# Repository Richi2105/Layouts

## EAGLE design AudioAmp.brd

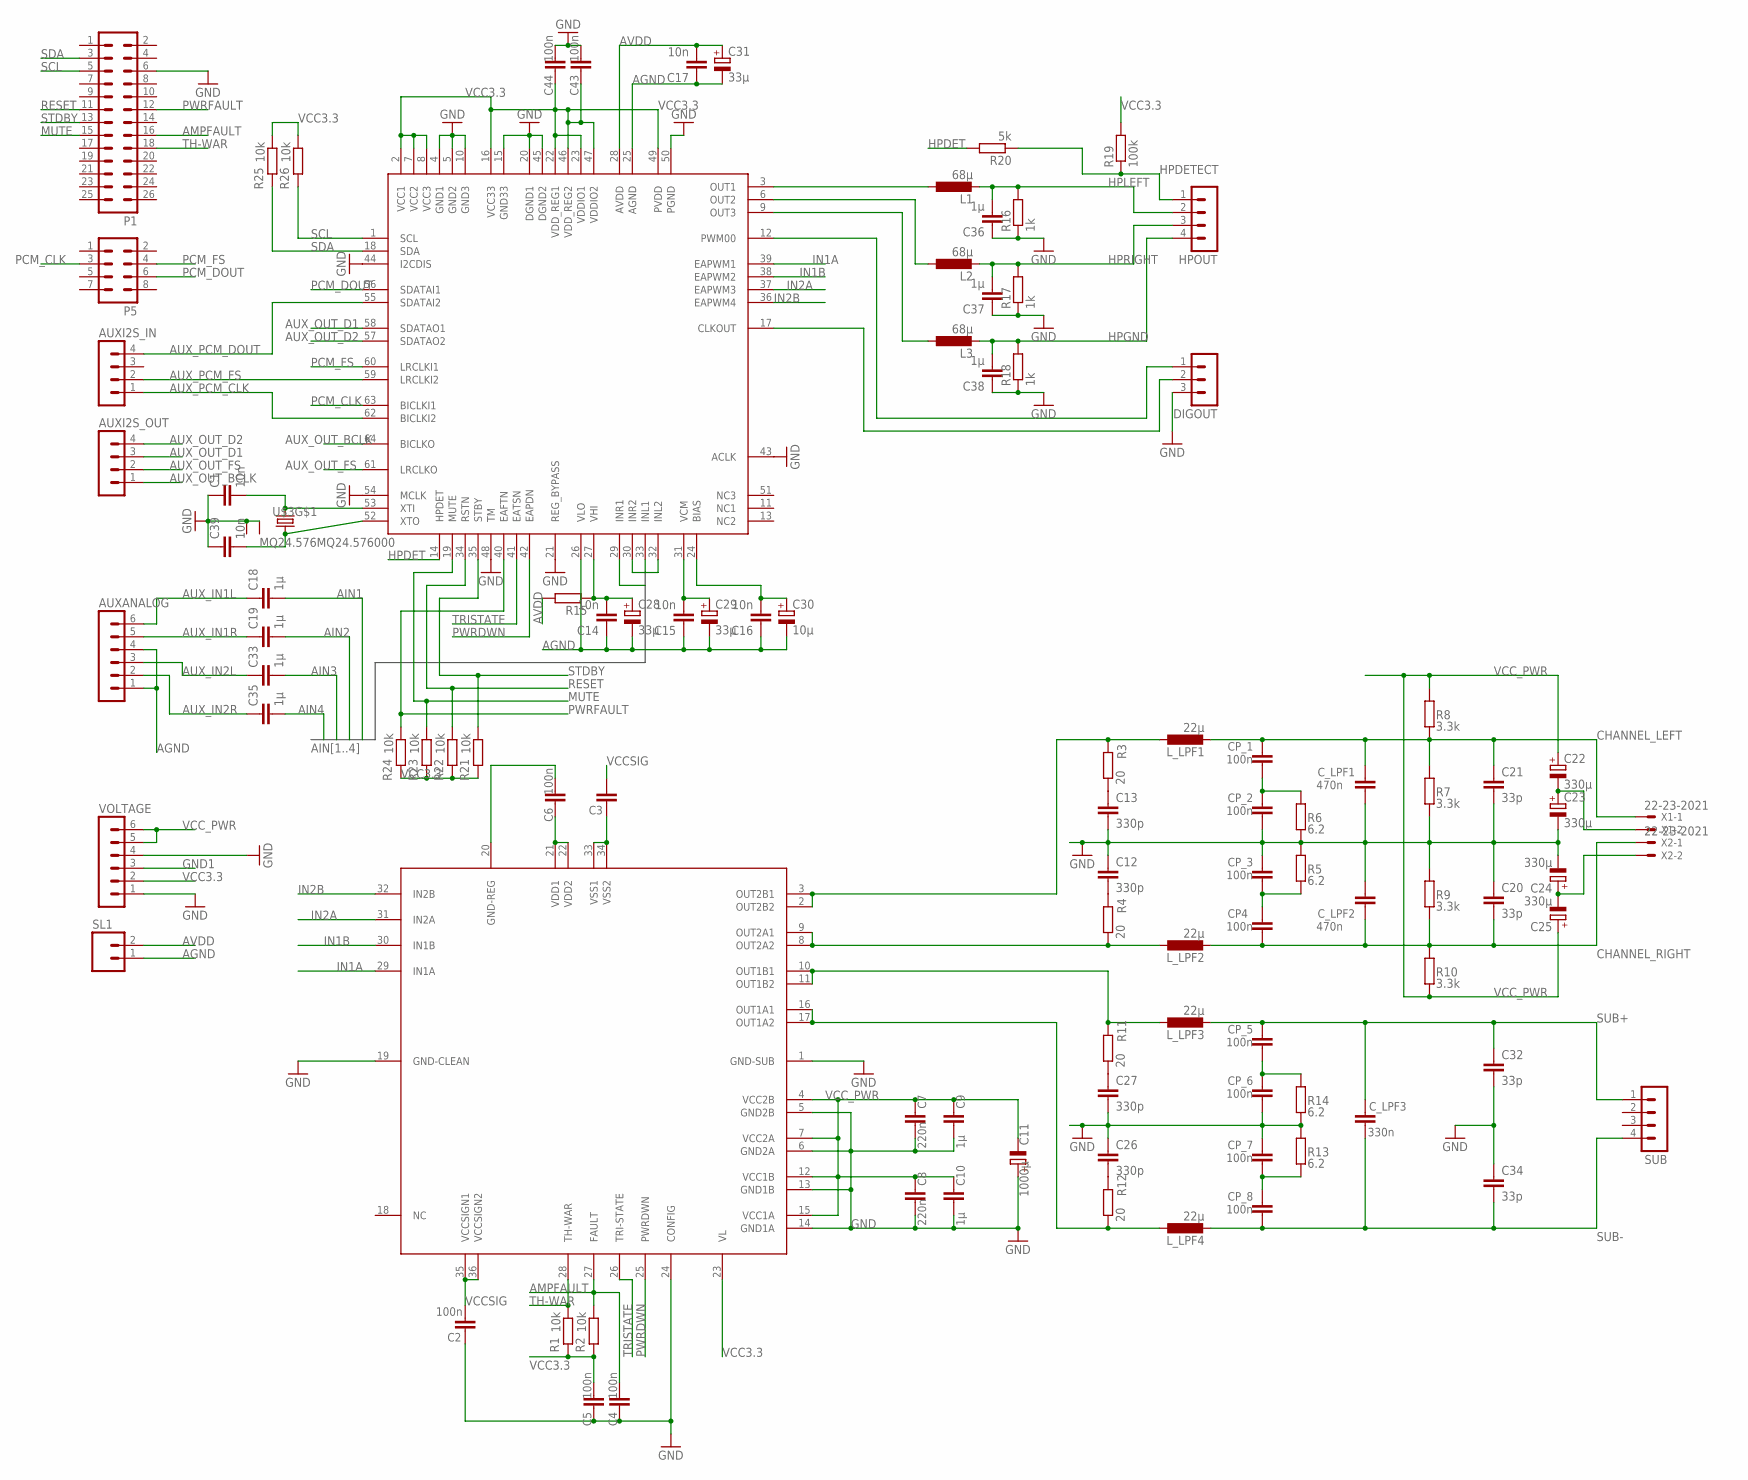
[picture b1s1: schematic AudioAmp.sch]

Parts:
AUXANALOG: MA06-1
AUXI2S_IN, AUXI2S_OUT: MA04-1
C1, C14, C15, C16, C17, C39: 10n; C1812
C2, C4, C5, C6, C43, C44: 100n; 2824
C3: C_EU_SMD2824; 2824
C7, C8: 220n; 2824
C9, C10: 1µ; 2824
C11: 1000µ; PANASONIC_J
C12, C13, C26, C27: 330p; C050-024X044
C18, C19, C33, C35, C36, C37, C38: 1µ; C050-045X075
C20, C21, C32, C34: 33p; C050-024X044
C22, C23, C24, C25: 330µ; E2,5-7
C28, C29, C31: 33µ; E2,5-5
C30: 10µ; E2,5-5
CP4: 100n; 2824
CP_1, CP_2, CP_3, CP_5, CP_6, CP_7, CP_8: 100n; 2824
C_LPF1, C_LPF2: 470n; 2824
C_LPF3: 330n; 2824
DIGOUT: MA03-1
HPOUT: MA04-1
L1, L2, L3: 68µ; 0204V
L_LPF1, L_LPF2, L_LPF3, L_LPF4: 22µ; PISR
P1: MA13-2
P5: MA04-2
R1, R2, R21, R22, R23, R24, R25, R26: 10k; R1206
R3, R4, R11, R12: 20; R1206
R5, R6, R13, R14: 6.2; R1206
R7, R8, R9, R10: 3.3k; R1206
R15: R-EU_0204/7; 0204/7
R16, R17, R18: 1k; 0204V
R19: 100k; 0204/7
R20: 5k; 0204/7
SL1: M02; 02P
SUB: MA04-1
U$1: STA510F; PSSO-36SD
U$2: STA321; LQFP-ST-64-2
U$3: MQ24.576MQ24.576000; MQ4
VOLTAGE: MA06-1
X1, X2: 22-23-2021

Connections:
AGND: AUXANALOG.1, AUXANALOG.4, C14.1, C15.1, C16.1, C17.1, C28.-, C29.-, C30.-, C31.-, SL1.1, U$2.25 (AGND), U$2.26 (VLO)
AIN1: C18.2, U$2.33 (INL1)
AIN2: C19.2, U$2.29 (INR1)
AIN3: C33.2, U$2.32 (INL2)
AIN4: C35.2, U$2.30 (INR2)
AMPFAULT: C4.2, P1.16, R2.1, U$1.27 (FAULT)
AUX_IN1L: AUXANALOG.6, C18.1
AUX_IN1R: AUXANALOG.5, C19.1
AUX_IN2L: AUXANALOG.3, C33.1
AUX_IN2R: AUXANALOG.2, C35.1
AUX_OUT_BCLK: AUXI2S_OUT.1, U$2.64 (BICLKO)
AUX_OUT_D1: AUXI2S_OUT.3, U$2.58 (SDATAO1)
AUX_OUT_D2: AUXI2S_OUT.4, U$2.57 (SDATAO2)
AUX_OUT_FS: AUXI2S_OUT.2, U$2.61 (LRCLKO)
AUX_PCM_CLK: AUXI2S_IN.1, U$2.62 (BICLKI2)
AUX_PCM_DOUT: AUXI2S_IN.4, U$2.55 (SDATAI2)
AUX_PCM_FS: AUXI2S_IN.2, U$2.59 (LRCLKI2)
AVDD: C17.2, C31.+, R15.2, SL1.2, U$2.28 (AVDD)
CHANNEL_LEFT: C21.1, CP_1.2, C_LPF1.2, L_LPF1.2, R7.2, R8.1, X1.1
CHANNEL_RIGHT: C20.2, CP4.1, C_LPF2.1, L_LPF2.2, R9.1, R10.2, X2.1
GND: C1.1, C2.1, C4.1, C5.1, C7.2, C8.2, C9.2, C10.2, C11.+, C12.1, C13.2, C20.1, C21.2, C23.-, C24.-, C26.1, C27.2, C32.2, C34.1, C36.1, C37.1, C38.1, C39.1, C43.2, C44.2, CP_2.1, CP_3.2, CP_6.1, CP_7.2, C_LPF1.1, C_LPF2.2, DIGOUT.3, P1.6, R5.2, R6.1, R7.1, R9.2, R13.2, R14.1, R16.1, R17.1, R18.1, U$1.1 (GND-SUB), U$1.5 (GND2B), U$1.6 (GND2A), U$1.13 (GND1B), U$1.14 (GND1A), U$1.19 (GND-CLEAN), U$1.24 (CONFIG), U$2.4 (GND1), U$2.5 (GND2), U$2.10 (GND3), U$2.15 (GND33), U$2.20 (DGND1), U$2.21 (REG_BYPASS), U$2.43 (ACLK), U$2.44 (I2CDIS), U$2.45 (DGND2), U$2.48 (TM), U$2.50 (PGND), U$2.54 (MCLK), U$3.P$2 (GND), U$3.P$4 (GND), VOLTAGE.1, VOLTAGE.4
GND1: VOLTAGE.3
HPDET: R20.2, U$2.14 (HPDET)
HPDETECT: HPOUT.1, R19.1, R20.1
HPGND: C38.2, HPOUT.4, L3.2, R18.2
HPLEFT: C36.2, HPOUT.2, L1.2, R16.2
HPRIGHT: C37.2, HPOUT.3, L2.2, R17.2
IN1A: U$1.29 (IN1A), U$2.39 (EAPWM1)
IN1B: U$1.30 (IN1B), U$2.38 (EAPWM2)
IN2A: U$1.31 (IN2A), U$2.37 (EAPWM3)
IN2B: U$1.32 (IN2B), U$2.36 (EAPWM4)
MUTE: P1.15, R23.1, U$2.19 (MUTE)
unnamed: C15.2, C29.+, U$2.31 (VCM)
unnamed: C16.2, C30.+, U$2.24 (BIAS)
unnamed: C39.2, U$2.52 (XTO), U$3.P$1 (1)
unnamed: C1.2, U$2.53 (XTI), U$3.P$3 (2)
unnamed: C3.1, U$1.33 (VSS1), U$1.34 (VSS2)
unnamed: C6.1, U$1.21 (VDD1), U$1.22 (VDD2)
unnamed: C6.2, U$1.20 (GND-REG)
unnamed: C12.2, R4.2
unnamed: C13.1, R3.1
unnamed: C22.-, C23.+, X1.2
unnamed: L_LPF2.1, R4.1, U$1.8 (OUT2A2), U$1.9 (OUT2A1)
unnamed: L_LPF1.1, R3.2, U$1.2 (OUT2B2), U$1.3 (OUT2B1)
unnamed: C26.2, R12.2
unnamed: C27.1, R11.1
unnamed: CP4.2, CP_3.1, R5.1
unnamed: CP_1.1, CP_2.2, R6.2
unnamed: C14.2, C28.+, R15.1, U$2.27 (VHI)
unnamed: C24.+, C25.-, X2.2
unnamed: L_LPF3.1, R11.2, U$1.10 (OUT1B1), U$1.11 (OUT1B2)
unnamed: CP_7.1, CP_8.2, R13.1
unnamed: CP_5.1, CP_6.2, R14.2
unnamed: L_LPF4.1, R12.1, U$1.16 (OUT1A1), U$1.17 (OUT1A2)
unnamed: L1.1, U$2.3 (OUT1)
unnamed: L2.1, U$2.6 (OUT2)
unnamed: L3.1, U$2.9 (OUT3)
unnamed: DIGOUT.1, U$2.12 (PWM00)
unnamed: DIGOUT.2, U$2.17 (CLKOUT)
PCM_CLK: P5.3, U$2.63 (BICLKI1)
PCM_DOUT: P5.6, U$2.56 (SDATAI1)
PCM_FS: P5.4, U$2.60 (LRCLKI1)
PWRDWN: U$1.25 (PWRDWN), U$2.42 (EAPDN)
PWRFAULT: P1.12, R24.1, U$2.40 (EAFTN)
RESET: P1.11, R22.1, U$2.34 (RSTN)
SCL: P1.5, R26.2, U$2.1 (SCL)
SDA: P1.3, R25.2, U$2.18 (SDA)
STDBY: P1.13, R21.1, U$2.35 (STBY)
SUB+: C32.1, CP_5.2, C_LPF3.2, L_LPF3.2, SUB.1
SUB-: C34.2, CP_8.1, C_LPF3.1, L_LPF4.2, SUB.4
TH-WAR: P1.18, R1.1, U$1.28 (TH-WAR)
TRISTATE: U$1.26 (TRI-STATE), U$2.41 (EATSN)
VCC3.3: C5.2, C43.1, C44.1, R1.2, R2.2, R19.2, R21.2, R22.2, R23.2, R24.2, R25.1, R26.1, U$1.23 (VL), U$2.2 (VCC1), U$2.7 (VCC2), U$2.8 (VCC3), U$2.16 (VCC33), U$2.22 (VDD_REG1), U$2.23 (VDDIO1), U$2.46 (VDD_REG2), U$2.47 (VDDIO2), U$2.49 (PVDD), VOLTAGE.2
VCCSIG: C2.2, C3.2, U$1.35 (VCCSIGN1), U$1.36 (VCCSIGN2)
VCC_PWR: C7.1, C8.1, C9.1, C10.1, C11.-, C22.+, C25.+, R8.2, R10.1, U$1.4 (VCC2B), U$1.7 (VCC2A), U$1.12 (VCC1B), U$1.15 (VCC1A), VOLTAGE.5, VOLTAGE.6

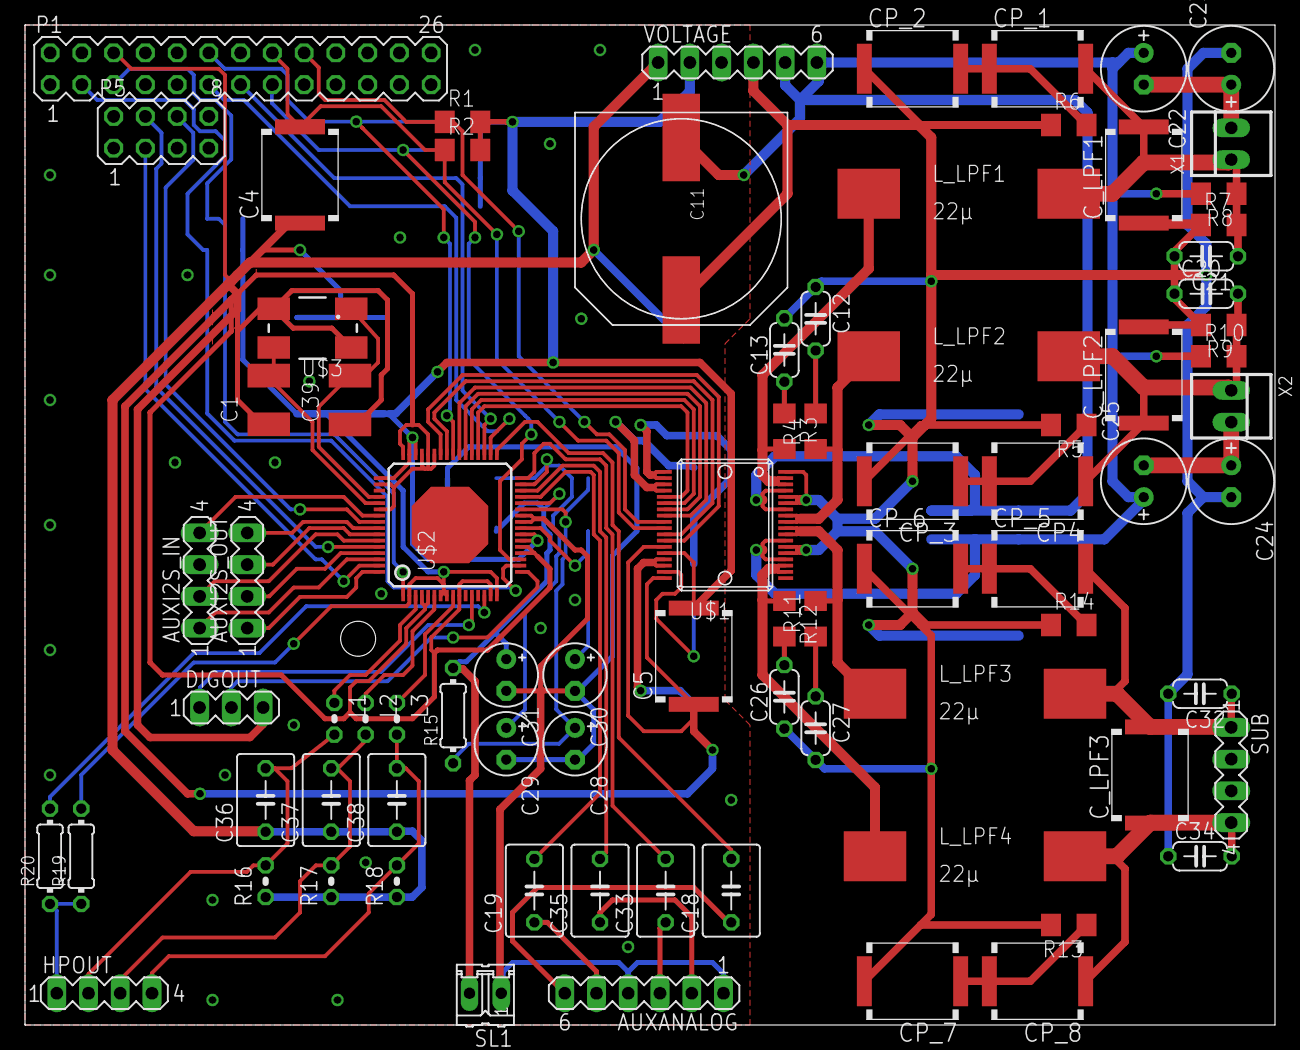
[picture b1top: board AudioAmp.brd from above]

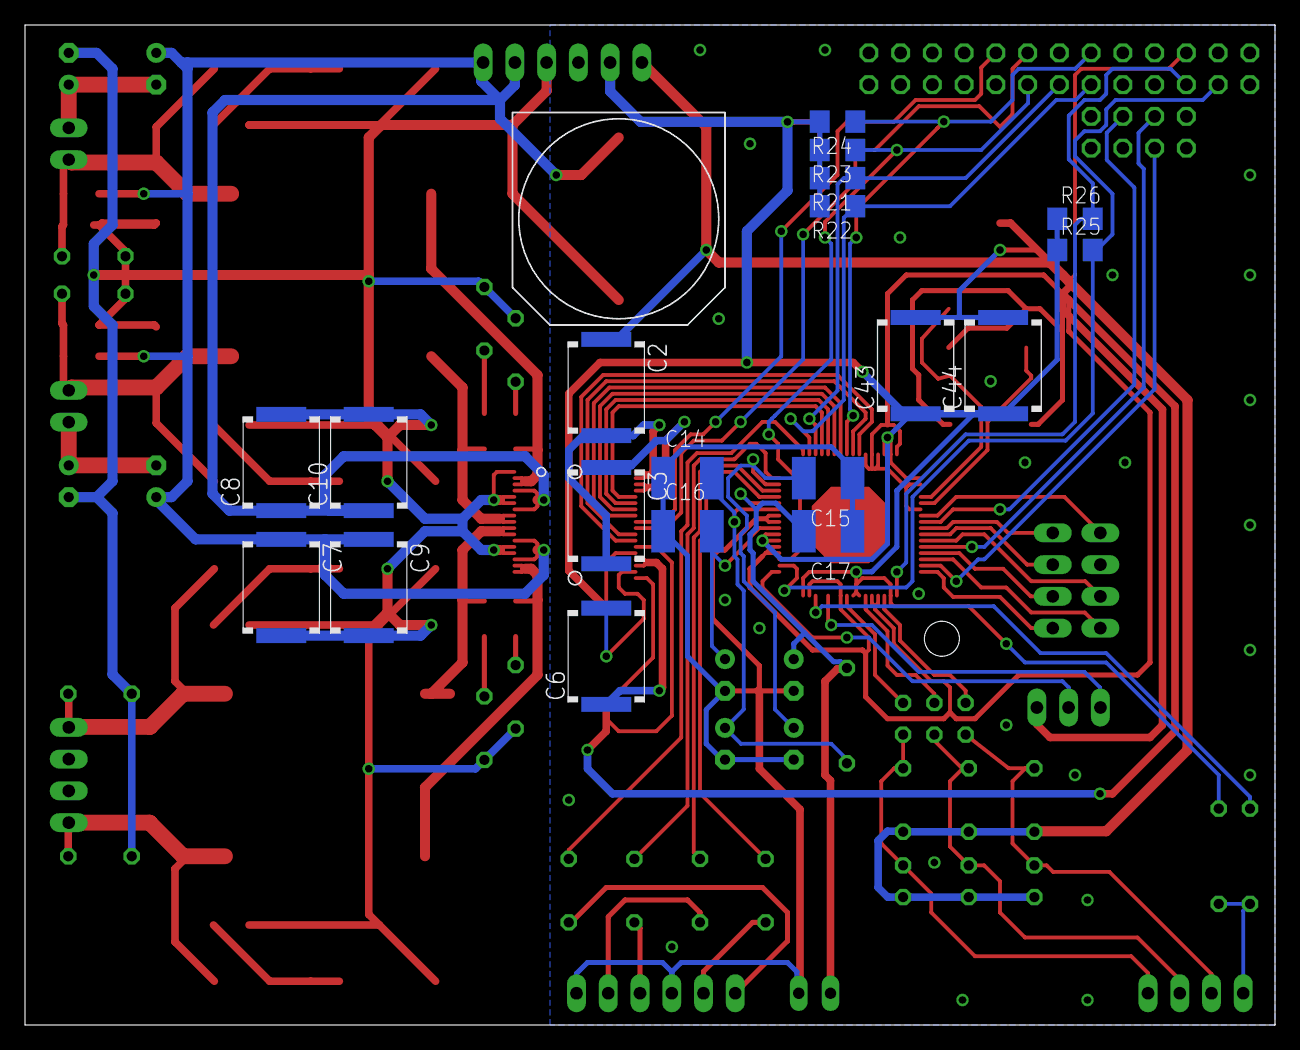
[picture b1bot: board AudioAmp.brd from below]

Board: 2 copper layers, 99.9 x 79.9 mm, 100 parts (19 on the bottom side), 74 nets.

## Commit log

2016-06-27 Amp layout done, process stage missing
2016-06-30 Todo: connect Thermal warning & Amp fault to P1 RPi
2016-07-01 todo: check analog supply grounding
2016-07-13 almost done
2016-07-14 ground wiring missing
2016-07-14 removed archive
2016-07-14 still messed
2016-07-15 done
